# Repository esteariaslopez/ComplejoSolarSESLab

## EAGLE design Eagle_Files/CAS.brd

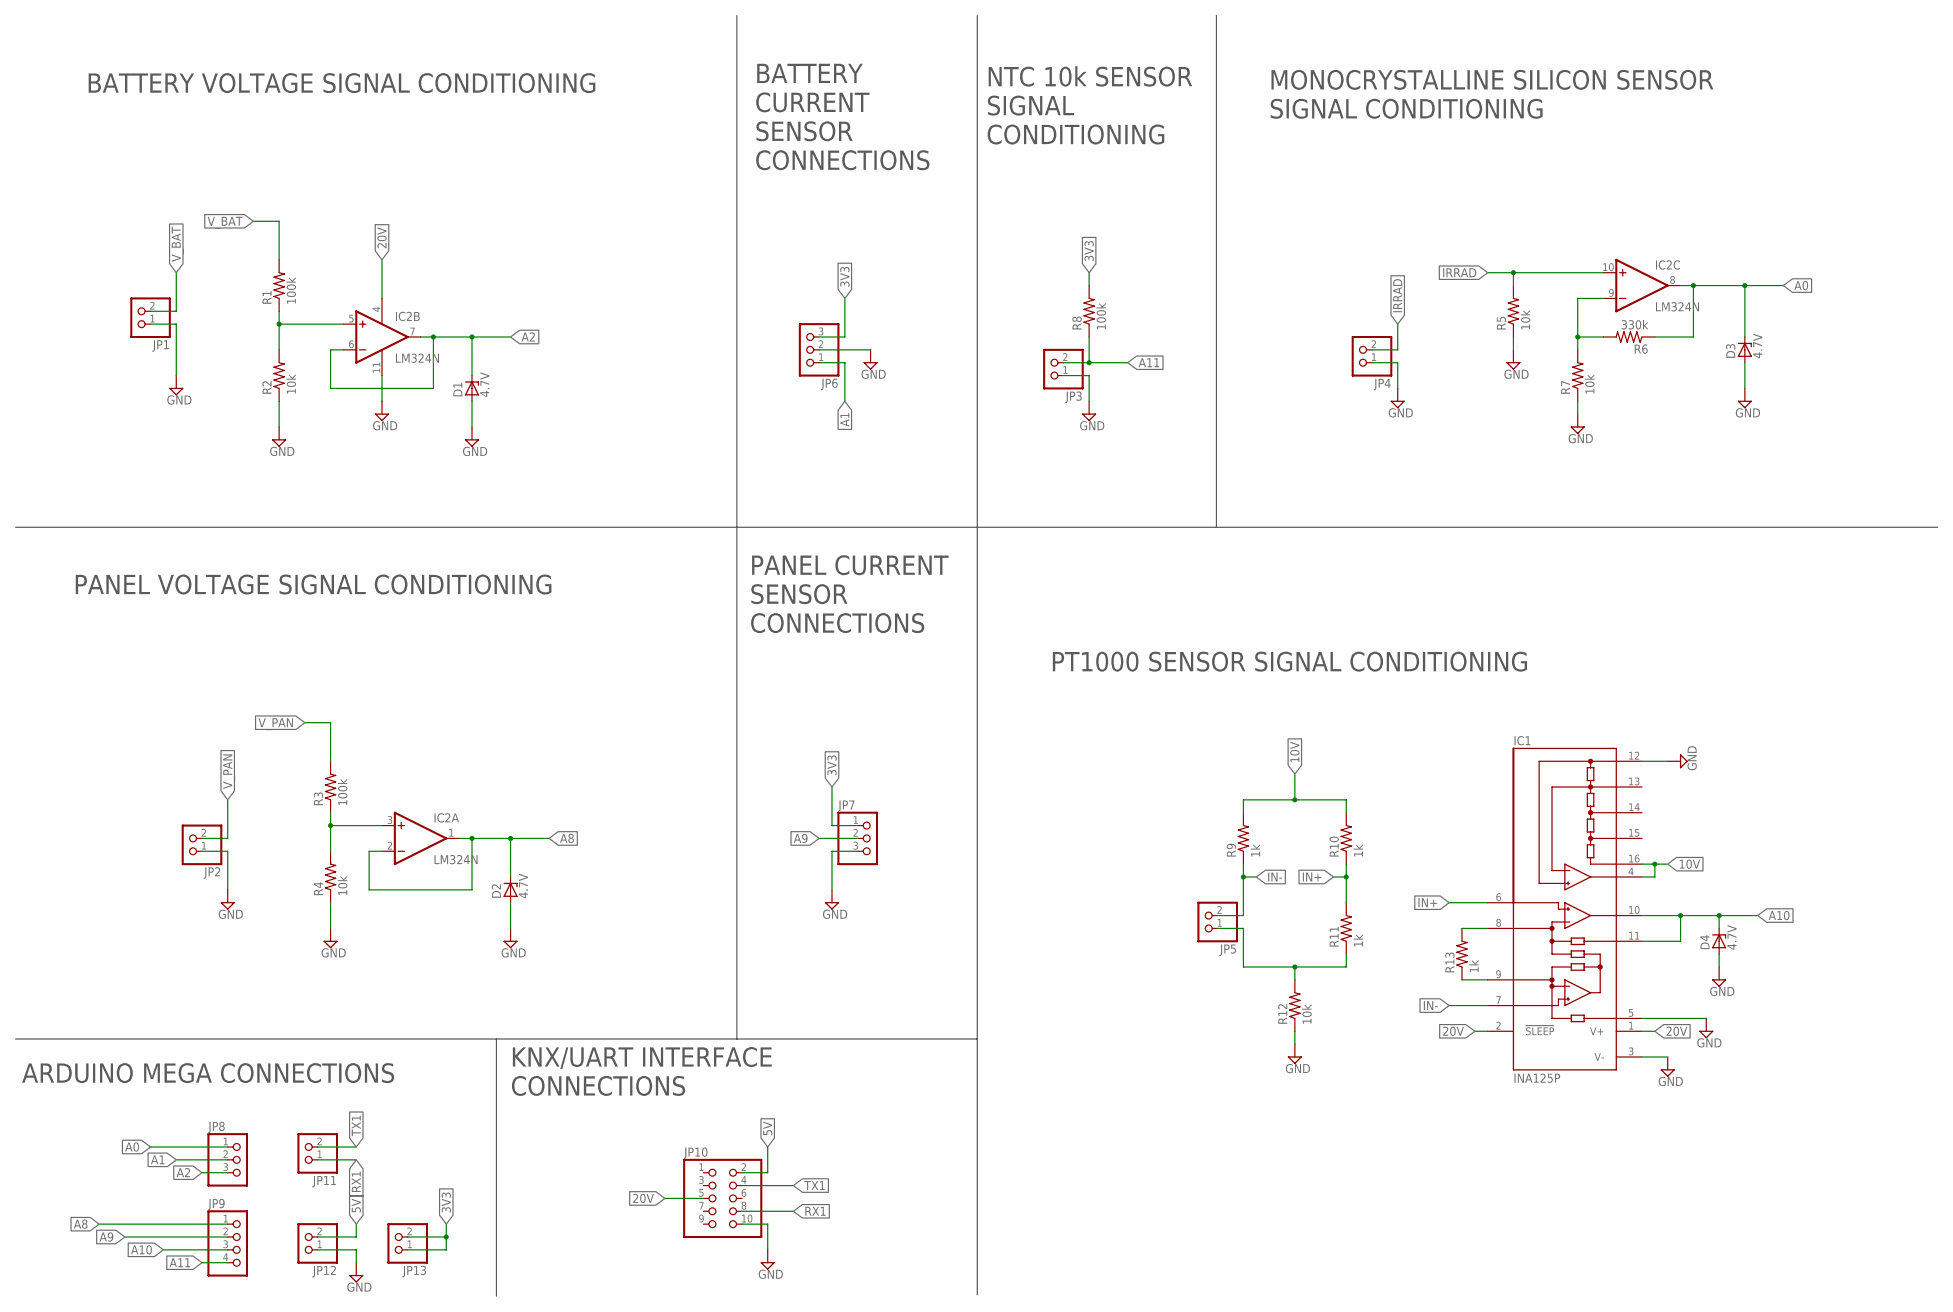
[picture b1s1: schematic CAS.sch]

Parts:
D1, D2, D3, D4: 4.7V; DO41Z10
IC1: INA125P; DIL16
IC2: LM324N; DIL14
JP1, JP2, JP3, JP4, JP5, JP11, JP12, JP13: PINHD-1X2; 1X02
JP6, JP7, JP8: PINHD-1X3; 1X03
JP9: PINHD-1X4; 1X04
JP10: PINHD-2X5; 2X05
R1, R3, R8: 100k; 0207/10
R2, R4, R5, R7, R12: 10k; 0207/10
R6: 330k; 0207/10
R9, R10, R11, R13: 1k; 0207/10

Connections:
3V3: JP6.3, JP7.1, JP13.1, JP13.2, R8.2
5V: JP10.2, JP12.2
10V: IC1.4 (REFOUT), IC1.16 (REF10), R9.2, R10.2
20V: IC1.1 (V+), IC1.2 (!SLEEP), IC2.4 (V+), JP10.5
A0: D3.C, IC2.8 (OUT), JP8.1, R6.1
A1: JP6.1, JP8.2
A2: D1.C, IC2.6 (-IN), IC2.7 (OUT), JP8.3
A8: D2.C, IC2.1 (OUT), IC2.2 (-IN), JP9.1
A9: JP7.2, JP9.2
A10: D4.C, IC1.10 (OUT), IC1.11 (SENSE), JP9.3
A11: JP3.2, JP9.4, R8.1
GND: D1.A, D2.A, D3.A, D4.A, IC1.3 (V-), IC1.5 (REF), IC1.12 (REFCOM), IC2.11 (V-), JP1.1, JP2.1, JP3.1, JP4.1, JP6.2, JP7.3, JP10.10, JP12.1, R2.1, R4.1, R5.1, R7.1, R12.1
IN+: IC1.6 (+IN), R10.1, R11.2
IN-: IC1.7 (-IN), JP5.2, R9.1
IRRAD: IC2.10 (+IN), JP4.2, R5.2
unnamed: IC2.3 (+IN), R3.1, R4.2
unnamed: IC2.5 (+IN), R1.1, R2.2
unnamed: IC2.9 (-IN), R6.2, R7.2
unnamed: IC1.8 (RG), R13.2
unnamed: IC1.9 (RG), R13.1
unnamed: JP5.1, R11.1, R12.2
RX1: JP10.8, JP11.1
TX1: JP10.4, JP11.2
V_BAT: JP1.2, R1.2
V_PAN: JP2.2, R3.2

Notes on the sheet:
BATTERY VOLTAGE SIGNAL CONDITIONING
PANEL VOLTAGE SIGNAL CONDITIONING
MONOCRYSTALLINE SILICON SENSOR SIGNAL CONDITIONING
PANEL CURRENT SENSOR CONNECTIONS
BATTERY CURRENT SENSOR CONNECTIONS
PT1000 SENSOR SIGNAL CONDITIONING
NTC 10k SENSOR SIGNAL CONDITIONING
ARDUINO MEGA CONNECTIONS
KNX/UART INTERFACE CONNECTIONS

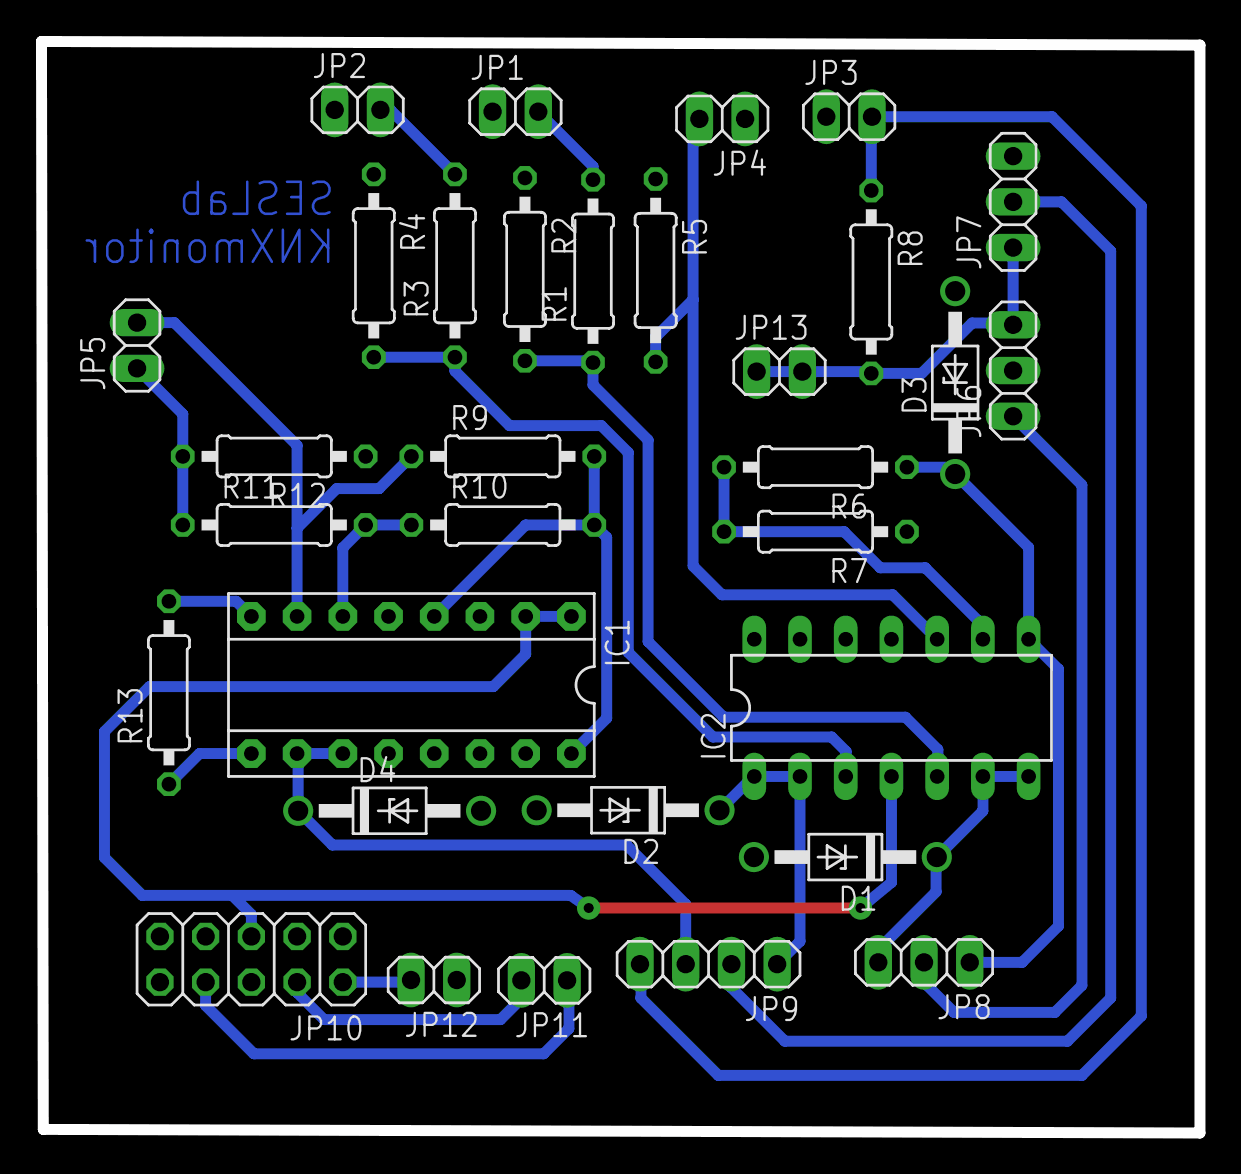
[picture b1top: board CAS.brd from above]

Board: 2 copper layers, 64.4 x 60.6 mm, 32 parts (0 on the bottom side), 25 nets.

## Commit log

2018-04-02 Sketch Arduino IDE (UNO) -Sense *NTC 10kOhm *ACS712T 5A -LCD print -Read period 1s
2018-04-02 -Table of preloaded NTC values
2018-04-02 -KNX library for Arduino
2018-04-03 LCD pin changed
2018-04-03 No changed
2018-04-03 SD datalogger added
2018-04-30 Some modifications
2018-04-30 First try with KnxDevice.h
2018-05-02 New Communications Objects added (Index 13, Index 14, Index 15) Timer.h library added to timer the sensor reading
2018-05-02 KNX functions added - need to be checked
2018-05-15 Added reading features, sensors calibrated
2018-05-15 Some functions fixed
2018-06-05 Lastest version
2018-06-05 Functions for Agilent Multimeter
2018-06-05 Matlab script to compare data among Arduino and Agilent Multimeter
2018-06-07 Some comments addered
2018-06-10 Some comments
2018-06-11 Irradiance and temperature
2018-06-11 changes to improve sense
2018-06-12 Ajuste de ecuacion para lectura de corrientes
2018-06-14 Last Sensors Calibration
2018-06-14 Files Updates
2018-06-16 Analog pins changed
